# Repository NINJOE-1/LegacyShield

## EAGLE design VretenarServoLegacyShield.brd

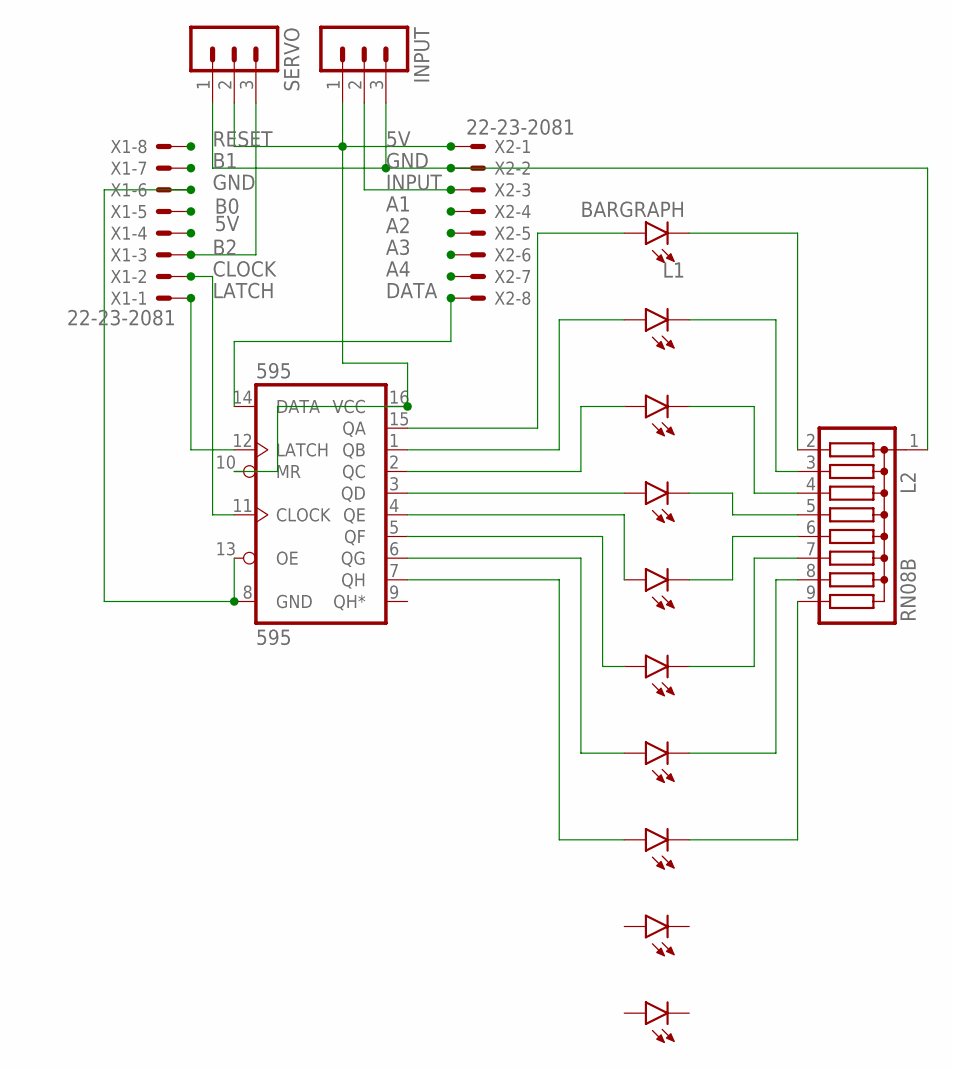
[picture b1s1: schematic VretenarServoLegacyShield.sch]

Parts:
595: 595; DIL16
INPUT: MA03-1
L1: BARGRAPH; LB10
L2: RN08B; RN-9
SERVO: MA03-1
X1, X2: 22-23-2081

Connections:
5V: 595.10 (MR), 595.16 (VCC), INPUT.1, SERVO.2, X1.4, X2.1
A1: X2.4
A2: X2.5
A3: X2.6
A4: X2.7
B0: X1.5
B1: X1.7
B2: SERVO.3, X1.3
CLOCK: 595.11 (CLOCK), X1.2
DATA: 595.14 (DATA), X2.8
GND: 595.8 (GND), 595.13 (OE), INPUT.3, L2.1, SERVO.1, X1.6, X2.2
INPUT: INPUT.2, X2.3
LATCH: 595.12 (LATCH), X1.1
unnamed: 595.15 (QA), L1.1 (A9)
unnamed: 595.1 (QB), L1.2 (A8)
unnamed: 595.2 (QC), L1.3 (A7)
unnamed: 595.3 (QD), L1.4 (A6)
unnamed: 595.4 (QE), L1.5 (A5)
unnamed: 595.5 (QF), L1.6 (A4)
unnamed: 595.6 (QG), L1.7 (A3)
unnamed: 595.7 (QH), L1.8 (A2)
unnamed: L1.20 (C9), L2.2
unnamed: L1.19 (C8), L2.3
unnamed: L1.18 (C7), L2.4
unnamed: L1.17 (C6), L2.5
unnamed: L1.16 (C5), L2.6
unnamed: L1.15 (C4), L2.7
unnamed: L1.14 (C3), L2.8
unnamed: L1.13 (C2), L2.9
RESET: X1.8

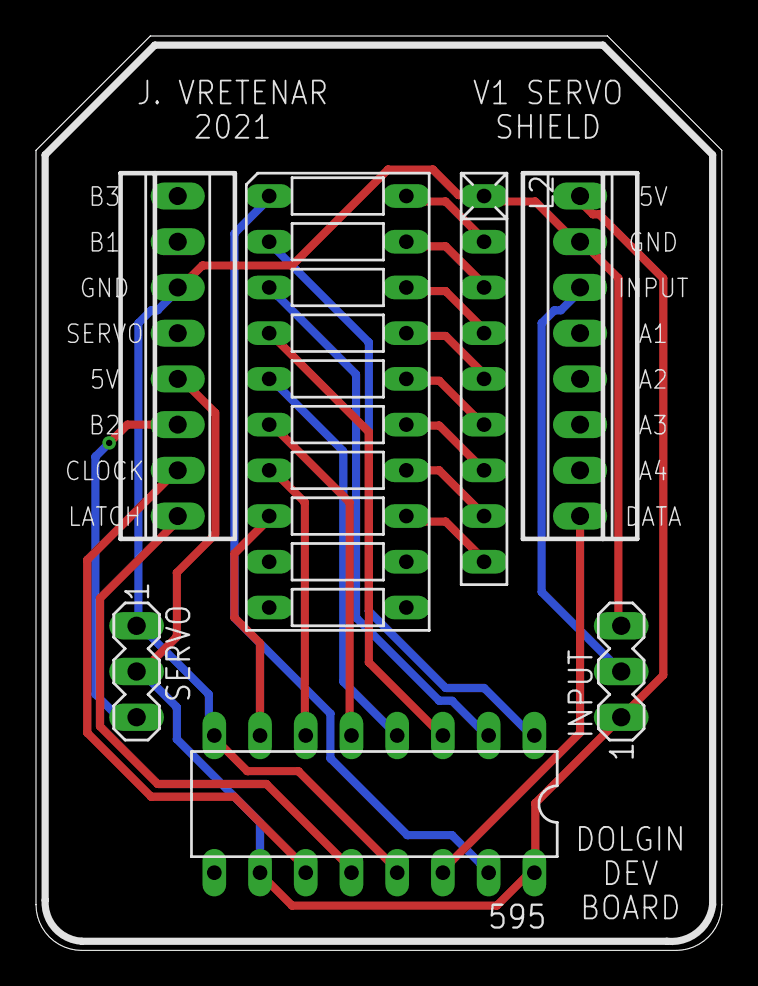
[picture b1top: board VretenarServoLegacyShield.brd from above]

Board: 2 copper layers, 38.1 x 50.8 mm, 8 parts (0 on the bottom side), 23 nets.

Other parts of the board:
U$9: ACES_LOGO_MEDIUM
